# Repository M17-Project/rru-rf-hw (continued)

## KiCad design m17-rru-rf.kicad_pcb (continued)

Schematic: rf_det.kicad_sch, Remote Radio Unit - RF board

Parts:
C77: 1u; C_0603_1608Metric; MPN CL10B105KB8NQNC
C78, C80, C83: 100n; C_0603_1608Metric; MPN C0603C104M5RAC7411
C79, C81, C82, C84, C85: 1n; C_0603_1608Metric; MPN C0603C102J5GAC7411
FB5: Bead; L_0603_1608Metric; MPN BLM18KG601SH1D
R35, R37: 52R3; R_0603_1608Metric; MPN CR0603-FX-52R3ELF
R36, R38: 499R; R_0603_1608Metric; MPN CRCW0603499RFKEA
TP16, TP17: TP; TestPoint_Pad_D1.5mm
U12, U13: AD8318; QFN65P400X400X100-17N; Mouser Part Number 584-AD8318ACPZ-R7

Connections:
/FWD_SENSE: TP16.1, U12.6 (VOUT), U12.7 (VSET); also elsewhere on the board
/Power supply/5V_OUT: C77.1, FB5.1; also elsewhere on the board
/REF_SENSE: TP17.1, U13.6 (VOUT), U13.7 (VSET); also elsewhere on the board
/RF coupler/FWD_RF: C81.1, R35.2; also elsewhere on the board
/RF coupler/REF_RF: C85.1, R37.2; also elsewhere on the board
/RF detectors/RF_DET_5V: C80.1, C82.1, FB5.2, U12.3 (VPSI_2), U12.4 (VPSI), U12.9 (VPSO), U12.16 (ENBL), U13.3 (VPSI_2), U13.4 (VPSI), U13.9 (VPSO), U13.16 (ENBL)
GND: C77.2, C78.2, C79.1, C80.2, C82.2, C83.2, C84.1, R35.1, R36.2, R37.1, R38.2, U12.1 (CMIP_2), U12.2 (CMIP_3), U12.8 (CMOP), U12.11 (CMIP_4), U12.12 (CMIP), U12.17 (EP), U13.1 (CMIP_2), U13.2 (CMIP_3), U13.8 (CMOP), U13.11 (CMIP_4), U13.12 (CMIP), U13.17 (EP); also elsewhere on the board
unnamed: C78.1, U12.5 (CLPF)
unnamed: C81.2, U12.14 (INHI)
unnamed: C79.2, U12.15 (INLO)
unnamed: R36.1, U12.10 (TADJ)
unnamed: C83.1, U13.5 (CLPF)
unnamed: C85.2, U13.14 (INHI)
unnamed: C84.2, U13.15 (INLO)
unnamed: R38.1, U13.10 (TADJ)

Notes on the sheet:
REF power sense
Decoupling
FWD power sense

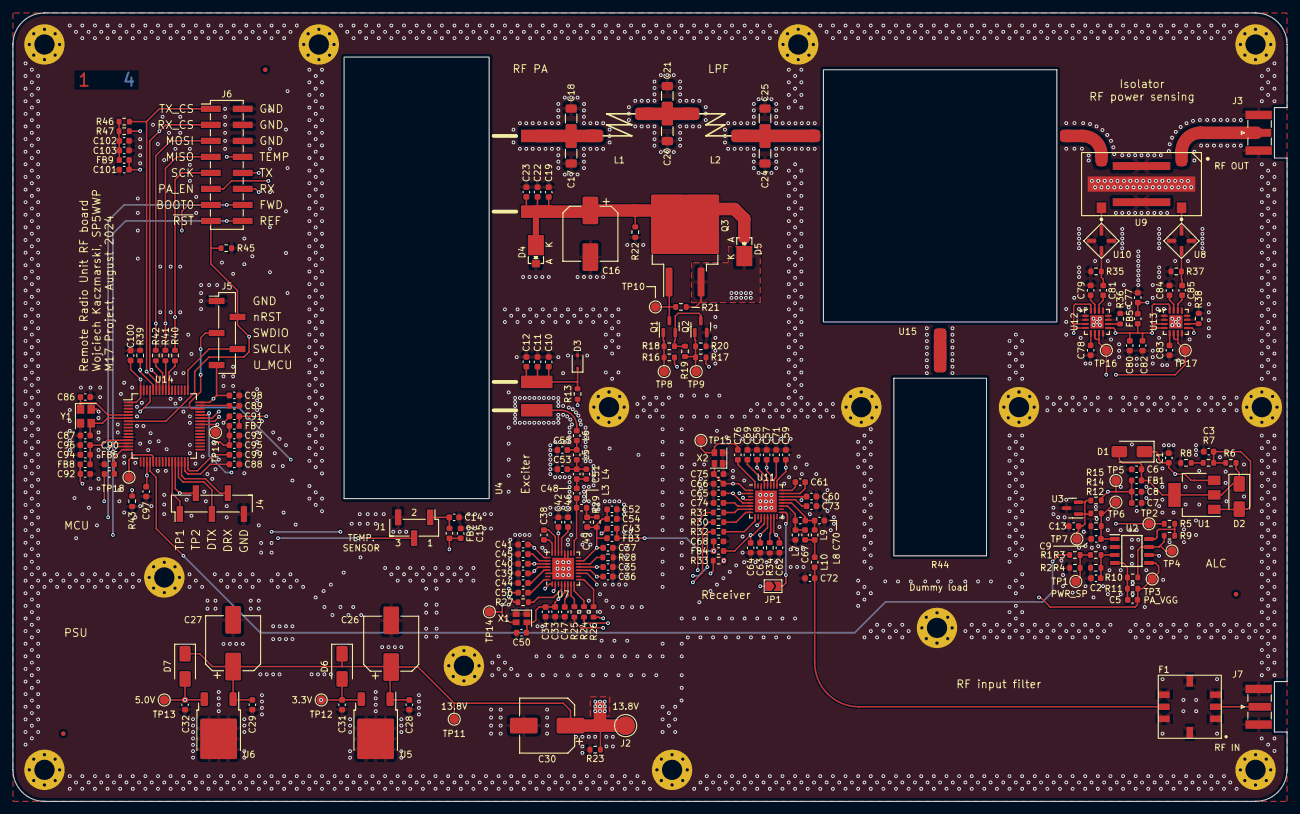
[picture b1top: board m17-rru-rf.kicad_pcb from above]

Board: 4 copper layers, 202.0 x 125.0 mm, 241 parts (0 on the bottom side), 117 nets.

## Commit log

2023-10-11 init
2023-10-14 LM317 protection diode location update
2023-10-14 partial PN update
2023-10-14 added missing 40MHz source
2023-10-15 caps' val update
    40MHz TCXO's max. output load is 10p||10k
2023-10-15 RF PA's Vgg signal fix
2023-10-15 significant updates
    - supply for the detector block changed from 3.3V to 5V
    - minor bugfixes
2023-10-15 PN update
2023-10-15 license update
2023-10-15 date and labels update
2023-10-15 `PWR_FLAG`, ERC cleanup
2023-10-16 TP updates, temp sensor added
2023-10-16 started pcb layout
2023-10-25 moved around a few components
2023-10-26 pcb update
2023-10-27 pcb update - PSU
2023-10-28 `DA15_CONN` pinout change
2023-10-30 pcb routing update
2023-10-30 silkscreen update
2023-10-30 date update
2023-10-31 license change
2023-10-31 some via fencing
2023-11-02 DRU fixes
2023-11-02 MPN/PN update
2023-11-02 minor silkscreen updates
2023-11-02 another silkscreen fix
2023-11-03 diode polarization bugfix
2023-11-03 small Top copper pour fix
2023-11-10 attenuators' PN update
2023-12-12 mechanical BOM
2023-12-15 generated BOM doc
2023-12-19 readme update
2024-01-18 WIP rev B
    - replaced R44-R46 with 22k
    - exposed BOOT0 at the DA15 connector
    - added a testpoint at DAC OUT2
    - added a buffer to the 40MHz reference oscillator
    - removed C2
    - bypassed R5 with a 100nF capacitor
2024-01-18 routed the 40MHz oscillator
2024-01-19 WIP rev B
    - added bleed resistors
    - power supply now uses linear regulators
    - routed RX_SAMP_CLK
    - added some decoupling at RF_PA_VDD
    - added some GND vias here and there
    - updated BOM
2024-01-19 L1, L6 - PN update
2024-01-19 updated PCB render
2024-01-19 silkscreen update (U2)
2024-01-19 Update README.md
    revision info
2024-01-20 minor footprint updates
2024-01-20 BOM typo fix
2024-01-20 minor changes
    footprint name change
2024-01-20 removed extra space
2024-01-20 removed capacitor
    removed cap between the 40MHz source and RX
2024-01-20 brought back the logo
2024-01-21 minor silkscreen update
2024-01-21 render update
2024-04-04 WIP rev C
2024-04-05 Rev C
    - lowpass at RF in
    - lowpass after RF PA
    - pulldown at TP2 (BOOT1)
    - CC1200 clocking fixed
    - PCB render/PDF update
2024-05-05 KiCAD version bump to 8.0.2
    - updated U9 PN
2024-05-07 C47/C74 PN update
2024-06-03 Update README.md
    new section: flashing the MCU over UART
2024-08-08 design updates
    - migrated to KiCAD 8.0.4
    - updated Vgg Zener diode from 5.1 to 4.7V
    - updated directional coupler's footprint
    - set RF lowpass filter caps' values
    - removed the outdated BOM CSV file
    - updated the PCB render and schematic PDF
